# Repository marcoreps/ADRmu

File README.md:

# ADR1000 10V standard

## Scope

Low cost 10V DC reference standard in DIN 41612 modular enclosure. Based on ovenized LTZ1000 / LTZ1000A or ADR1000A zener diodes. Fits into standard 100x160mm project boxes too. The most promising strategies for configuring the zener and buffering the output are accommodated. Includes a high isolation DC-DC converter to attenuate the effects of common mode current.

## TODO

Align JP and R designators

Remove JPB and JPH enumeration

add lt5400 and other gain resistor options

discrete push-pull driver

snubber for the DC-DC converter?

## Assembly advice

Recommended 5:7 transformer (pri:sec) when using 12V input

## Spec speculations

After initial settling, tempco adjustment, continuously powered on, no ambient temperatures outside of specified range

### Output Voltage Stability (± µV/V):

24 hour: < 0.3

30 day: < 0.4

90 day: < 0.8

1 year: < 1.0

### Output Voltage Noise (0.1 - 10 Hz)(±µV/V rms)

< 0.02

### Output Voltage Tempco (±µV/V/K)

< 0.04

### Short circuit current (mA)

9-11

### Power consumption (W)

\< 2W

### Isolation (to DCin, Chassis)

\> 10 000 MΩ

< 1000 pF

### Output Protection

Output can be shorted indefinitely with battery life derating. Output protected against ESD and input up to 60V.

### Specified Temperature Range (°C)

15 - 35

### Oerational Temperature Range (°C)

-10 - 40

## Measured results
| SN    | U202  | .1-10Hz Noise   | Tempco 15-35°C    |  24h Stab  |  30d Stab  |  90d Stab  |  1yr Stab  |
| ---   | ----  | --------------  | ---------------   | ---------- | ---------- | ---------- | ---------- |
|       |       | \[µV/V rms\]    | \[µV/V/k\]        | \[µV/V\]   | \[µV/V\]   | \[µV/V\]   | \[µV/V\]   |
|   1   | ADR   | [0.0139][1]     |                   | 0.25       | 0.4        |            |            |
| ~~2~~ |~~LTZ-A~~| ~~[0.0175][2]~~|                  |            |            |            |            |
|   3   | LTZ-A | [0.0201][3]     | [-0.024][3tc]     |            |            |            |            |
|   4   |ADR1001| [0.0275][4]     | [-0.133][4tc]     |            |            |            |            |
| ~~5~~ |~~ADR~~|~~[0.0119][5]~~  |~~[+0.015][5tc]~~  |            |            |            |            |
| ~~7~~ |~~ADR~~|~~[0.0125][7]~~  |~~[+0.032][7tc]~~  |            |            |            |            |
|   9   |  ADR  |  [0.0121][9]    |  [+0.156][9tc]    |            |            |            |            |
|~~107~~|~~ADR~~|                 |~~[+0.049][107tc]~~|            |            |            |            |
|~~108~~|~~ADR~~|~~[0.0163][108]~~|~~[+0.030][108tc]~~|            |            |            |            |
|~~10~~ |~~ADR~~|~~[0.0115][10]~~ |~~[-0.028][10tc]~~ |            |            |            |            |
|  11   | ADR   | [0.0129][11]    | [+0.015][11tc]    |            |            |            |            |
|  12   | ADR   | [0.0116][12]    |                   |            |            |            |            |
|~~13~~ |~~ADR~~|~~[0.0132][13]~~ |~~[-0.024][13tc]~~ |            |            |            |            |
|~~F731B~~  |~~DH80417B~~| ~~[0.0272][731]~~  |       |            |            |            |            |
|   6   | ADR   |                 | [-0.018][6tc]     |            |            |            |            |
|~~14~~ |~~LTZ-A~~|               |~~[+0.025][14tc]~~ |            |            |            |            |
|  15   |  ADR  |   [0.0123][15]  |                   |            |            |            |            |
|  20   | LTZ-A |                 | -0.018            |            |            |            |            |
 
[1]:/results/ADRmu1_LFnoise.png
[2]:/results/ADRmu2_LFnoise.png
[3]:/results/ADRmu3_LFnoise.png
[4]:/results/ADRmu4_LFnoise_improved.png
[5]:/results/ADRmu5_LFnoise.png
[7]:/results/ADRmu7_LFnoise.png
[9]:/results/ADRmu9_LFnoise.png
[10]:/results/ADRmu10_LFnoise.png
[11]:/results/ADRmu11_LFnoise.png
[12]:/results/ADRmu12_LFnoise.png
[13]:/results/ADRmu13_LFnoise.png
[13]:/results/ADRmu15_LFnoise.png
[108]:/results/ADRmu108_LFnoise.png
[731]:/results/Fluke731B_LFnoise.png

[3tc]:/results/ADRmu3_TC.ipynb
[4tc]:/results/ADRmu4_TC.ipynb
[5tc]:/results/ADRmu5_TC.ipynb
[7tc]:/results/ADRmu7_TC.ipynb
[9tc]:/results/ADRmu9_TC.ipynb
[10tc]:/results/ADRmu10_TC.ipynb
[11tc]:/results/ADRmu11_TC.ipynb
[12tc]:/results/ADRmu12_TC.ipynb
[13tc]:/results/ADRmu13_TC.ipynb
[107tc]:/results/ADRmu107_TC.ipynb
[108tc]:/results/ADRmu108_TC.ipynb
[14tc]:/results/ADRmu14_TC.ipynb
[6tc]:/results/ADRmu6_TC.ipynb

Strikethrough: Device no longer in my possession

## Initial drift & burn-in
| SN  | PCB  |      U202      | Powered on | Preparation | Initial ΔV | Hours to plateau | .1-10Hz noise before | Special |
| --- | ---- | -------------- | ---------- | ----------- | ---------- | ---------------- | -------------------- |---------|
|   1 | 0.4  | ADR1000A 2017  | Jul 2021   |1yr dummy circuit| no data|                  |                      | VPG golden network |
|   2 | 0.4  |    LTZ1000A    | Apr 2022   | none        | no data    |                  |                      | LTZ1000A w/ VPG foil |
|   3 | 0.5  |    LTZ1000A    | Mar 2022   | none        | no data    |                  |                      | Cheapest LTZ variant |
|   4 |0.5SE |    ADR10001    | May 2022   | none        | no data    |                  |                      | ~~Popcorn noise~~ Healed? |
|   5 | 0.9  | ADR1000A 2022  | Jan 2023   | 7d 150°C b&b|            |                  |                      | Gone to new owner |
|   7 | 0.9  | ADR1000A 2022  | Jan 2023   | 7d 150°C b&b|            |                  |                      | No trim resistors |
|   9 | 0.9  | ADR1000A 2022  | Jan 2023   | none        | 1.1 µV/V   | 310              |                      | VPG golden network |
| 107 | 0.9  | ADR1000A 2018  | Dec 2022   | none        | 3.8 µV/V   | 640              |                      | Transplant to 108 |
| 108 | 0.9  | ADR1000A 2018  | Dec 2022   | none        | 3.8 µV/V   | 640              |                      | Gone to new owner |
|  10 | 0.9  | ADR1000A 2022  | Feb 2023   | none        |            |                  |                      | On/off cylcing 48h |
|  11 | 0.9  | ADR1000A 2022  | Feb 2023   |7d dummy circuit|         |                  |                      | No trim resistors |
|  12 | 0.9  | ADR1000A 2022  | Feb 2023   |7d in situ b&b|           |                  |                      | On/off cylcing 24h |
|  13 | 0.9  | ADR1000A 2022  | Feb 2023   |             |            |                  |                      | Ultrasonic cleaned |
|   6 | 1.1  | ADR1000A 2022  | Mar 2023   |30d dummy circuit|        |                  |                      | Chinese SMT assembly |
|  14 | 1.1  | LTZ1000A 2020  | Mar 2023   | none        |            |                  |                      | Chinese SMT assembly |
|  15 | 1.1  | LTZ1000A 2020  | Mar 2023   | none        |            |                  |                      | Chinese SMT assembly |
|  44 | 1.1  | LTZ1000A 2020  | Mar 2023   | none        |            |                  |                      | Chinese SMT assembly |
|  20 | 1.1  | LTZ1000A 2020  | Sep 2023   | none        |            |                  |                      | Chinese SMT assembly |

## Trim levels

The PCB is prepared for various configurations to adapt to different needs and part availabilities. Here's what I have built so far:

| SN  | U202 | R213 / Pin4 | R214 / Pin5 | R220 / Pin3 | Oven divider      | R225 / Iz Down | R223 / Iz Up | 10V gain divider |
| --- | ---- | ----------- | ----------- | ----------- | ----------------- | -------------- | ------------ | ---------------- |
|   1 | ADR  | 1445 95.3R  | 1445 61.9k  | 0R          | 1445 13 ratio     | open           | open         | 1445 2 ratio     |
|   2 |LTZ-A | Z201 100R   | 61.9k  Foil | SMD Foil    | VHD200 13 ratio   |                |              | VHD200 2.5 ratio |
|   3 |LTZ-A | 100R TOMC   | 50k S102    | 100R TOMC/5 | TDP10k 13.5 ratio | open           | 230k RN73    | TDP10k 2.5 ratio |
|   4 |ADR1k1| 100R VHP100T| integrated  | integrated  | integrated        |                |              | integrated       |
|   5 | ADR  | Alpha MCY   | Alpha MAY   | 0R          | TDP10k 11.5 ratio | open           | 470k RN73    | TDP10k 2 ratio   |
|   7 | ADR  | Z201        | Z201        | 0R          | TDP10k            | open           | open         | TDP10k 2 ratio   |
|   9 | ADR  | 1445 95.3R  | 1445 61.9k  | 0R          | 1445 13 ratio     | open           | open         | 1445 2 ratio     |
| 107 | ADR  | Z201T       | Z202T       | 0R          | TOMC10k 11.5 ratio| 200k RN73      | open         | TDP10k 2 ratio   |
| 108 | ADR  | Z201T       | Z202T       | 0R          | TOMC10k 11.5 ratio|                |              | TDP10k 2 ratio   |
|  10 | ADR  | RCK02       | RCK02       | 0R          | TDP10k 11.5 ratio | 493k RN73      | open         | TDP10k 2 ratio   |
|  11 | ADR  | Z201T       | Z201T       | 0R          | TDP10k 11.5 ratio |                |              | TDP10k 2 ratio   |
|  12 | ADR  | RCK02       | RCK02       | 0R          | TDP10k 12 ratio   | 1M             | open         | TDP10k 2 ratio   |
|  13 | ADR  | RCK02       | RCK02       | 0R          | TDP10k 11.5 ratio | open           | 1M           | TDP10k 2 ratio   |
|   6 | ADR  | PTF56       | PTF56       | 0R          | TDP10k 11.5 ratio |                |              | TDP10k 2 ratio   |
|  14 |LTZ-A | TDP         | 1% ax metal | TDP         | TDP10k 12   ratio | open           | open         | TDP10k 2.5 ratio |
|  15 |      |             |             |             |                   |                |              |                  |
|  44 | ADR  | Z201T       | Z202T       | 0R          | TDP10k 11.5 ratio | 900k           | open         | TDP10k 2 ratio   |
|  20 |LTZ-A | 100R TDP    | 40k Prec WW | 16.667R TDP | TDP10k 11.5 ratio | open           | 1M           | TDP10k 2.5 ratio |

## Raw Vz of 10 parts in datasheet default circuit, warmed up for a few minutes but not burnt in
| SN  |   Type  | Datecode |     Vz    | 
| --- | ------- | -------- | --------- |
| \#1 | ADR1000 | 2108     | 6.6556730 |
| \#8 | ADR1000 | 2108     | 6.6545676 |
| \#9 | ADR1000 | 2108     | 6.6531460 |
| \#10| ADR1000 | 2108     | 6.6609841 |
| \#11| ADR1000 | 2108     | 6.6690263 |
| \#12| ADR1000 | 2108     | 6.6534043 |
|   5 | ADR1000 | 2209     | 6.6457519 |
|   8 | ADR1000 | 2209     | 6.6509818 |
|   3 | ADR1000 | 1839     | 6.6707478 |
| \#7 | ADR1000 | 2108     | 6.6545726 |

### ADR1000 & Vishay 1445 All-in-one Resistor Network

My SN 1 is built this way. This is a no-brainer or easy mode. When I got my first glimpse at the ADR1000 datasheet I went straight to Vishay Foil Resistors and ordered an all-in-one resistor network with all the critical resistors from the datasheet plus a simple divider for buffering the 6.62V output to 10V ([Custom network specification][1445]). By specifying at least 2 ppm/°C TC tracking for the two critical dividers I am guaranteed great performance. And thanks to the hermetically sealed DIP14 package I expect little long term drift from the resistors. This solution comes at a hefty price and is not effortlessly adjustable after assembly.

[1445]:/datasheets/322146_p1-4_1445_Marco_Reps.pdf

### LTZ1000A & Discrete Vishay Foil Resistors

My SN 2 is built this way. This is probably the most popular way of building LTZ1000 voltage standards (i.e. [xDevs KX][kx]). Digikey carries quite a few hermetically sealed Vishay Bulk Metal Foil resistors ~~without MOQ these days~~ not any more LAME!, giving you all the design freedom. The two most critical parts are the LTZ-temperature-configuration divider i.e. 13k/1k and the 7.1V to 10V buffer divider i.e. 2k/5k. For these two I used hermetically sealed Vishay VHD200 dividers. These have guaranteed TC tracking and little long term drift. The remaining LTZ-configuration resistors i.e. 70k, 70k, 120R are not very critical. For best performance you can add an additional resistor to LTZ pin 3 to improve the Vrefs tempco, see "Adjusting Temperature Coefficient in Unstabilized Applications" in the LTZ1000 datasheet. 20 Ohm seems to be a reasonable approximation, suitable for most LTZs. In my case I determined 18 Ohm to be an optimal resistor with a TC peak at the oven setpoint. Careful, this additional resistor, if equipped, has a lot of influence on zener voltage and should be of high quality.

[kx]:https://xdevs.com/article/kx-ref/

### LTZ1000A & Thin film arrays

My SN 3 and 20 are built this way. This variant is inspired by Datron Wavetek 7000 DCV Standards ([EEVBlog forum thread][w7000]) and as such it has proven itself over a long time. Here the most critical voltage dividers for the LTZ1000 temperature and the 7->10V gain are implemented through an arrangement of monolithic thin film resistor arrays and their fantastic tracking temperature coefficients. Furthermore the overall output voltage tempco is fine-tuned after assembly through trim resistors R225 / R223. SN 3 is one of the cheapest ADRmus in my comparison, yet one of the most stable ones.

[w7000]:https://www.eevblog.com/forum/metrology/(3300)-wavetek-7000-the-hidden-gemstone/

### ADR1000 & Thin film arrays

Most of my ADRmus are built this way. This is the most cost-effective way to build a great performance 10V DC Standard. The same techniques that worked for LTZ in the past also apply to ADR1000, only the specific resistor values are slightly different. Based on my early ADR1000 samples I can see significantly longer initial settling times of ADR1000, which can be improved simply by power cycling a part in its default circuit (30 minutes off, 30 minutes on for a week). This new part exhibits lower low frequency noise than LTZ. A 10V buffer circuit with a low noise op amp and thin film arrays ([Excess Noise in Thin Film and Metal Foil Resistor Networks][beev]) passes this advantage right on to the output. 

[beev]:https://arxiv.org/abs/2109.02448

### ADR1001

I have been given one very early sample of this new part, so my results may not reflect the final parts performance. This new all-in-one ovenized zener reference & buffer makes it easier than ever before to deploy a high performance, environmentally tolerant voltage reference with few external parts and little research. My sample showed some popcorn noise at first ([Screenshot][popcorn]), which I seemingly improved by keeping the part powered on, externally heated to 110°C for a few weeks. This extreme measure made it impossible to judge early drift. Long-term drift and tempco now seem to fall easily within the datasheet spec. LF noise of the 10V output still appears to be slightly elevated, but the datasheet only specifies this for the 6P6 output. Overall this part is not the greatest performer in my comparison, it lacks a way of fine-tuning, but it's by far the easiest to use and its efficient overall heater makes it interesting for portable devices.

[popcorn]:/results/ADRmu4_LFnoise_popcorn.png

## Results

### Raw data

Unprocessed CSV files can be found here https://github.com/marcoreps/multiinstrumentalist/tree/master/csv These show direct readings by digital voltmeters, which are subject to temperature variations, adjustments and even modifications, resulting in large deviations of readings.

### Processed data

To attenuate voltmeter errors from the measurements, we use the mathematical difference between an ADRmu reading and the average of many ADRmu readings that were taken at the same time, with the same voltmeter. These results can be found here https://github.com/marcoreps/ADRmu/tree/main/results

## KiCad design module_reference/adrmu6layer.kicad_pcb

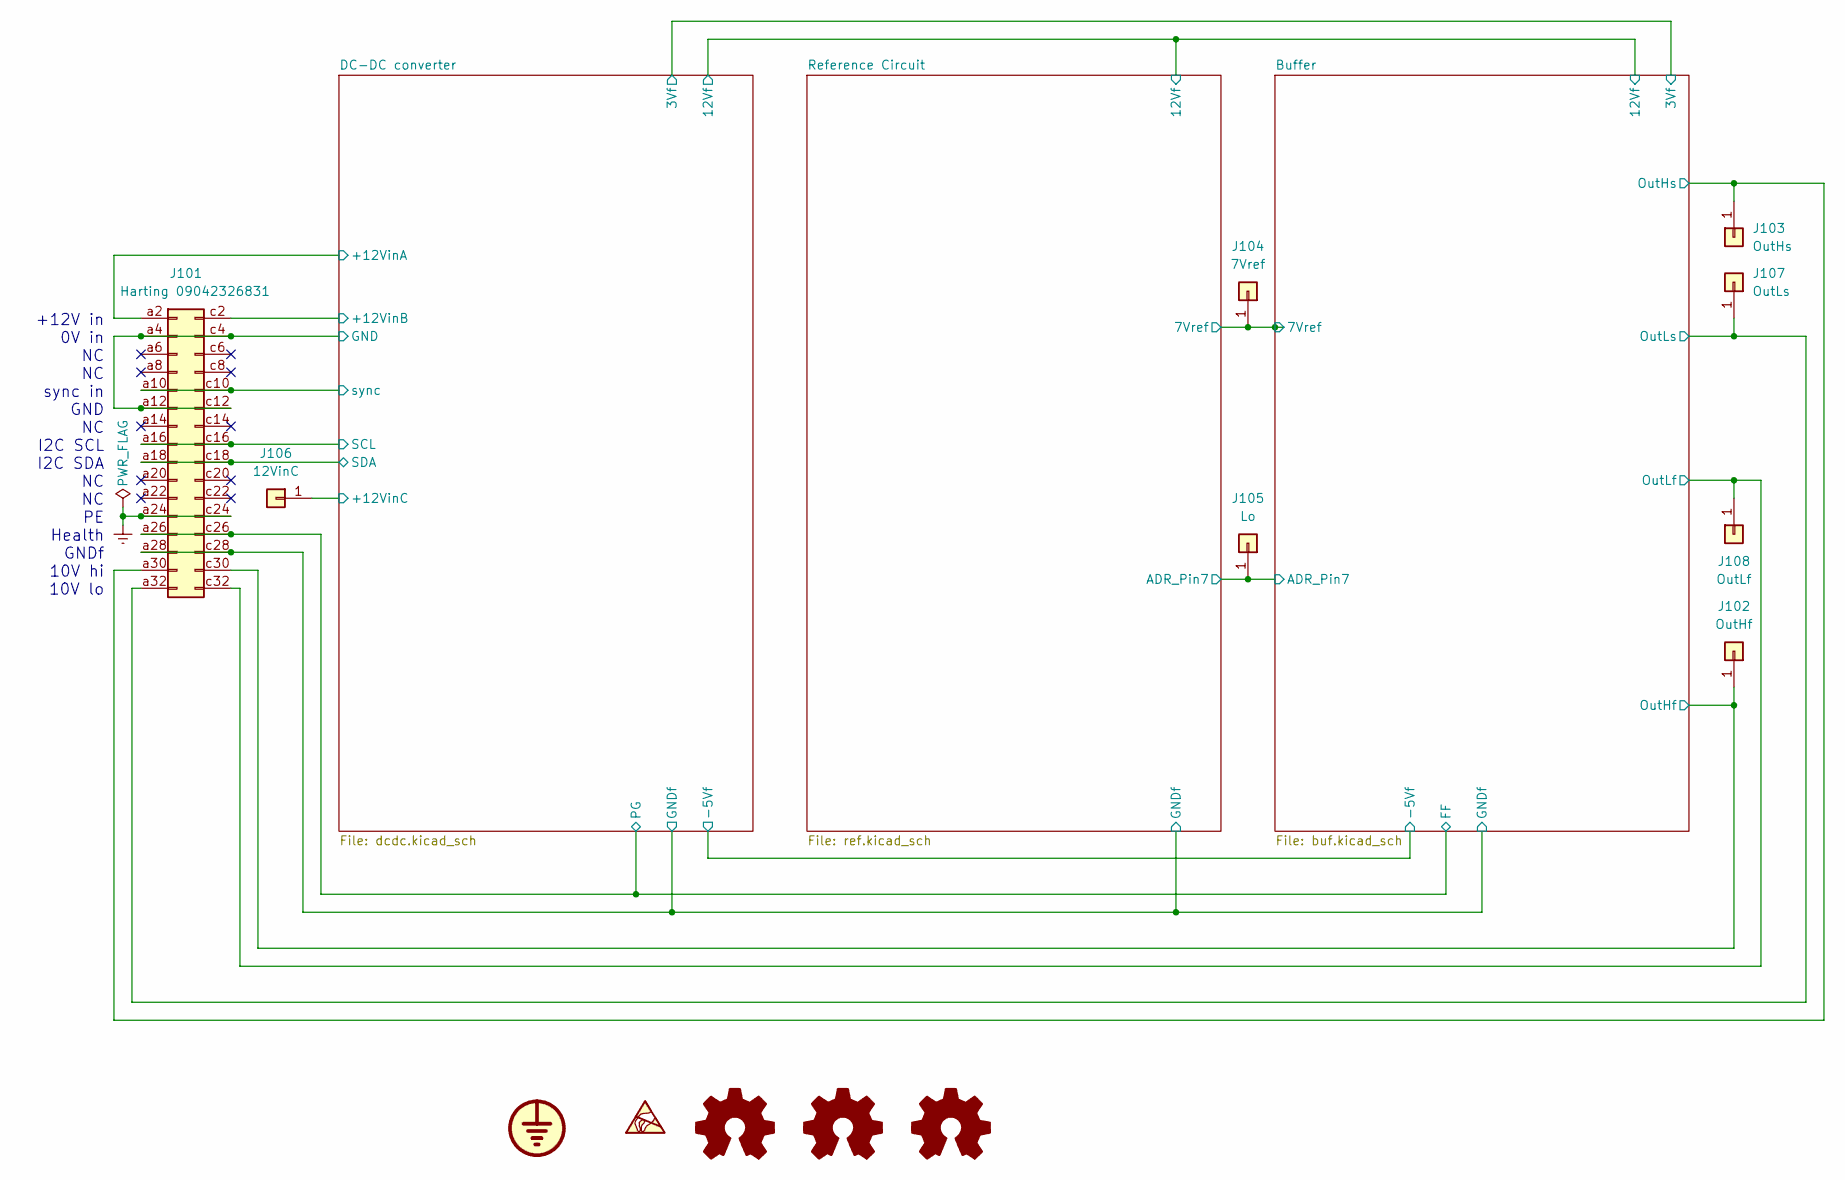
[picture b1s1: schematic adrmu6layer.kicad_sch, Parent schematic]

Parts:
J101: Harting 09042326831; DIN41612_D_2x16_Male_Horizontal_THT
J102: OutHf; SolderWire-1sqmm_1x01_D1.4mm_OD2.7mm
J103: OutHs; SolderWire-1sqmm_1x01_D1.4mm_OD2.7mm
J104: 7Vref; SolderWire-1sqmm_1x01_D1.4mm_OD3.9mm
J105: Lo; SolderWire-1sqmm_1x01_D1.4mm_OD3.9mm
J106: 12VinC; SolderWire-1sqmm_1x01_D1.4mm_OD2.7mm
J107: OutLs; SolderWire-1sqmm_1x01_D1.4mm_OD2.7mm
J108: OutLf; SolderWire-1sqmm_1x01_D1.4mm_OD2.7mm
SYM101: OSMU; osmu_logo
SYM102: SYM_ESD_Small; ESD-Logo_8.9x8mm_SilkScreen
SYM103: Logo_Open_Hardware_Small; OSHW-Logo2_9.8x8mm_SilkScreen
SYM104: Logo_Open_Hardware_Small; KiCad-Logo2_6mm_SilkScreen
SYM105: Logo_Open_Hardware_Small; moin_logo

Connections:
/Buffer/ADR_Pin7: J105.1; also elsewhere on the board
/Buffer/FF: J101.a26, J101.c26; also elsewhere on the board
/Buffer/GNDf: J101.a28, J101.c28; also elsewhere on the board
/Buffer/OutHf: J101.c30, J102.1; also elsewhere on the board
/Buffer/OutHs: J101.a30, J103.1; also elsewhere on the board
/Buffer/OutLf: J101.c32, J108.1; also elsewhere on the board
/Buffer/OutLs: J101.a32, J107.1; also elsewhere on the board
/DC-DC converter/+12VinA: J101.a2; also elsewhere on the board
/DC-DC converter/+12VinB: J101.c2; also elsewhere on the board
/DC-DC converter/+12VinC: J106.1; also elsewhere on the board
/DC-DC converter/SCL: J101.a16, J101.c16; also elsewhere on the board
/DC-DC converter/SDA: J101.a18, J101.c18; also elsewhere on the board
/DC-DC converter/sync: J101.a10, J101.c10; also elsewhere on the board
/Reference Circuit/7Vref: J104.1; also elsewhere on the board
Earth: J101.a24, J101.c24; also elsewhere on the board
GND: J101.a4, J101.a12, J101.c4, J101.c12; also elsewhere on the board

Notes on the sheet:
+12V in 0V in NC NC sync in GND NC I2C SCL I2C SDA NC NC PE Health GNDf 10V hi 10V lo

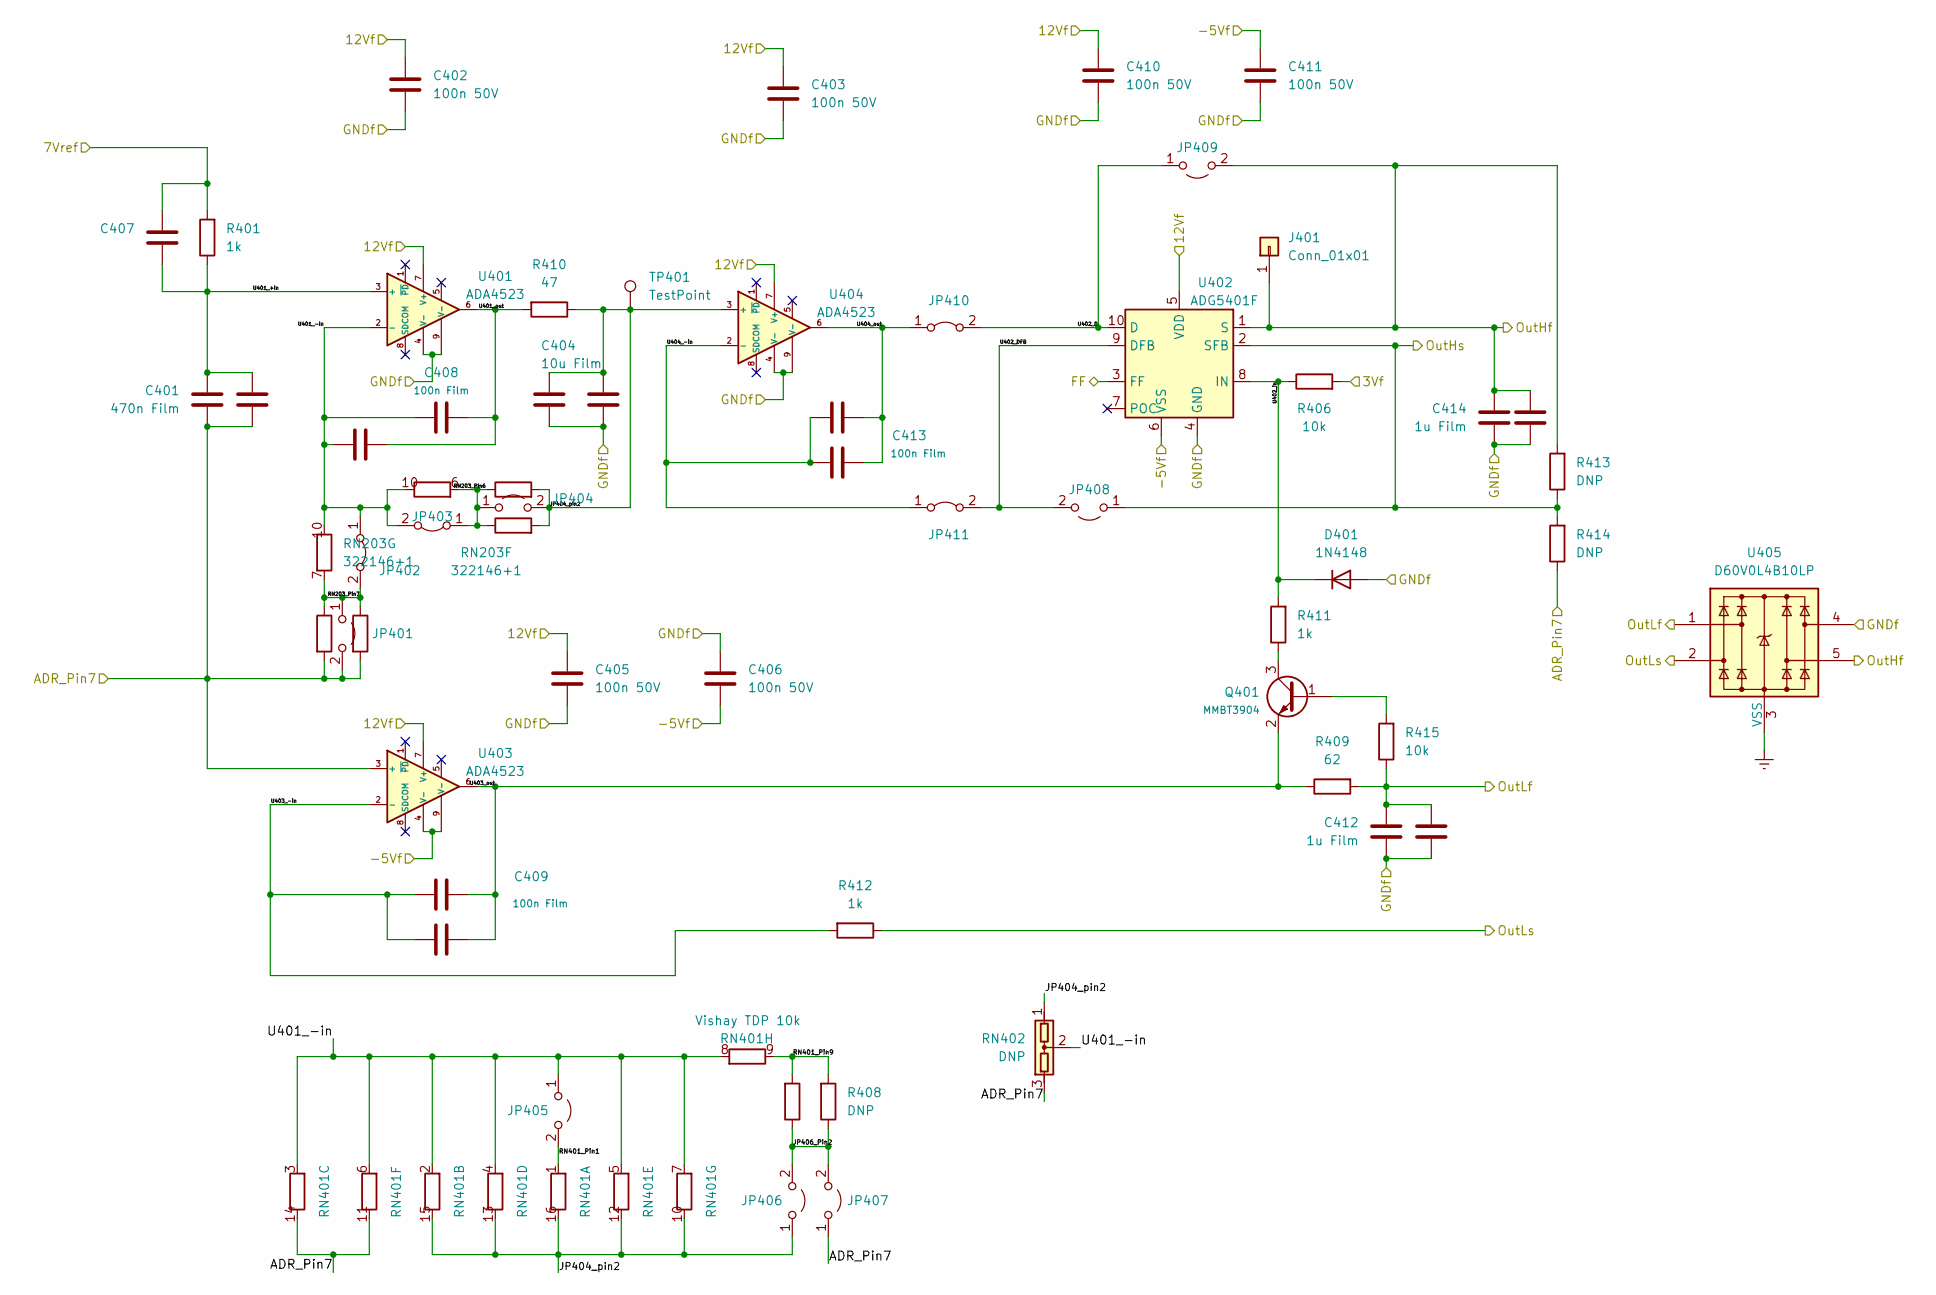
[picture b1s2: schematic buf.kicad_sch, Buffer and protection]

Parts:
C401: 470n Film; C_Rect_L7.2mm_W3.5mm_P5.00mm_FKS2_FKP2_MKS2_MKP2
C402, C403, C405, C406, C410, C411, C416, C417, C419: 100n 50V; C_0603_1608Metric
C404: 10u Film; C_Rect_L7.2mm_W11.0mm_P5.00mm_FKS2_FKP2_MKS2_MKP2
C407: DNP; C_0805_2012Metric
C408, C409, C413: 100n Film; C_Rect_L7.2mm_W2.5mm_P5.00mm_FKS2_FKP2_MKS2_MKP2
C412, C414: 1u Film; C_Rect_L4.6mm_W5.5mm_P2.50mm_MKS02_FKP02
C415: 470n; C_1206_3216Metric
C418: 22u 25V; C_1206_3216Metric
C420, C421: 1u; C_0805_2012Metric
D401: 1N4148; D_SOD-123
J401: Conn_01x01; SolderWirePad_1x01_SMD_1x2mm
JP401, JP404, JP405, JP406, JP407, JP408, JP409: Jumper_2_Open; SolderJumper-2_P1.3mm_Open_RoundedPad1.0x1.5mm
JP402, JP403, JP410, JP411: Jumper_2_Bridged; SolderJumper-2_P1.3mm_Bridged_RoundedPad1.0x1.5mm
Q401: MMBT3904; SOT-23
R401, R411, R412: 1k; R_0805_2012Metric
R402, R405: 0; Crystal_HC52-U_Vertical
R403, R404: 0; R_0805_2012Metric
R406, R415: 10k; R_0805_2012Metric
R407: DNP; Crystal_HC52-U_Vertical
R408, R413, R414: DNP; R_0805_2012Metric
R409: 62; R_0805_2012Metric
R410: 47; R_0805_2012Metric
RN203: 322146+1; VPG322146+1
RN401: Vishay TDP 10k; DIP-16_W7.62mm
RN402: DNP; Resonator-3Pin_W10.0mm_H5.0mm
TP401: TestPoint; TestPoint_THTPad_2.0x2.0mm_Drill1.0mm
U401, U403, U404: ADA4523; LFCSP-8-1EP_3x3mm_P0.5mm_EP1.6x2.34mm
U402: ADG5401F; LFCSP-10
U405: D60V0L4B10LP; Diodes_UDFN-10_1.0x2.5mm_P0.5mm

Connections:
/Buffer/3Vf: R406.2; also elsewhere on the board
/Buffer/12Vf: C402.2, C403.2, C405.2, C410.2, U401.7 (V+), U402.5 (VDD), U403.7 (V+), U404.7 (V+); also elsewhere on the board
/Buffer/-5Vf: C406.1, C411.2, U402.6 (VSS), U403.4 (V-), U403.9 (V-); also elsewhere on the board
/Buffer/ADR_Pin7: C401.1, C415.2, JP401.2 (B), JP407.1 (A), R402.2, R403.2, R414.1, RN401.11 (R6.2), RN401.14 (R3.2), RN402.3, U403.3 (+); also elsewhere on the board
/Buffer/FF: U402.3 (FF); also elsewhere on the board
/Buffer/GNDf: C402.1, C403.1, C404.2, C405.1, C406.2, C410.1, C411.1, C412.2, C414.2, C418.2, C420.2, C421.2, D401.2 (A), U401.4 (V-), U401.9 (V-), U402.4 (GND), U404.4 (V-), U404.9 (V-), U405.4; also elsewhere on the board
/Buffer/JP404_pin2: C404.1, C418.1, JP404.2 (B), JP406.1 (A), R404.2, R405.2, R410.1, RN401.10 (R7.2), RN401.12 (R5.2), RN401.13 (R4.2), RN401.15 (R2.2), RN401.16 (1.2), RN402.1, TP401.1, U404.3 (+)
/Buffer/JP406_Pin2: JP406.2 (B), JP407.2 (B), R407.1, R408.1
/Buffer/OutHf: C414.1, C421.1, J401.1, JP409.2 (B), R413.2, U402.1 (S), U405.5; also elsewhere on the board
/Buffer/OutHs: JP408.1 (A), R413.1, R414.2, U402.2 (SFB); also elsewhere on the board
/Buffer/OutLf: C412.1, C420.1, R409.2, R415.1, U405.1; also elsewhere on the board
/Buffer/OutLs: R412.1, U405.2; also elsewhere on the board
/Buffer/RN203_Pin6: JP403.1 (A), JP404.1 (A), R404.1, R405.1, RN203.6 (R6.1)
/Buffer/RN203_Pin7: JP401.1 (A), JP402.2 (B), R402.1, R403.1, RN203.7 (R7.1)
/Buffer/RN401_Pin1: JP405.2 (B), RN401.1 (1.1)
/Buffer/RN401_Pin9: R407.2, R408.2, RN401.9 (8..2)
/Buffer/U401_+in: C401.2, C407.1, C415.1, R401.1, U401.3 (+)
/Buffer/U401_-in: C408.2, C416.2, JP402.1 (A), JP403.2 (B), JP405.1 (A), RN203.10 (R7.2), RN401.2 (R2.1), RN401.3 (R3.1), RN401.4 (R4.1), RN401.5 (R5.1), RN401.6 (R6.1), RN401.7 (R7.1), RN401.8 (1.1), RN402.2, U401.2 (-)
/Buffer/U401_out: C408.1, C416.1, R410.2, U401.6
/Buffer/U402_D: JP409.1 (A), JP410.2 (B), U402.10 (D)
/Buffer/U402_DFB: JP408.2 (B), JP411.2 (B), U402.9 (DFB)
/Buffer/U402_in: D401.1 (K), R406.1, R411.2, U402.8 (IN)
/Buffer/U403_-in: C409.2, C417.2, R412.2, U403.2 (-)
/Buffer/U403_out: C409.1, C417.1, Q401.2 (E), R409.1, U403.6
/Buffer/U404_-in: C413.2, C419.2, JP411.1 (A), U404.2 (-)
/Buffer/U404_out: C413.1, C419.1, JP410.1 (A), U404.6
/Reference Circuit/7Vref: C407.2, R401.2; also elsewhere on the board
Earth: U405.3 (VSS), U405.8 (VSS); also elsewhere on the board
unnamed: Q401.1 (B), R415.2
unnamed: Q401.3 (C), R411.1

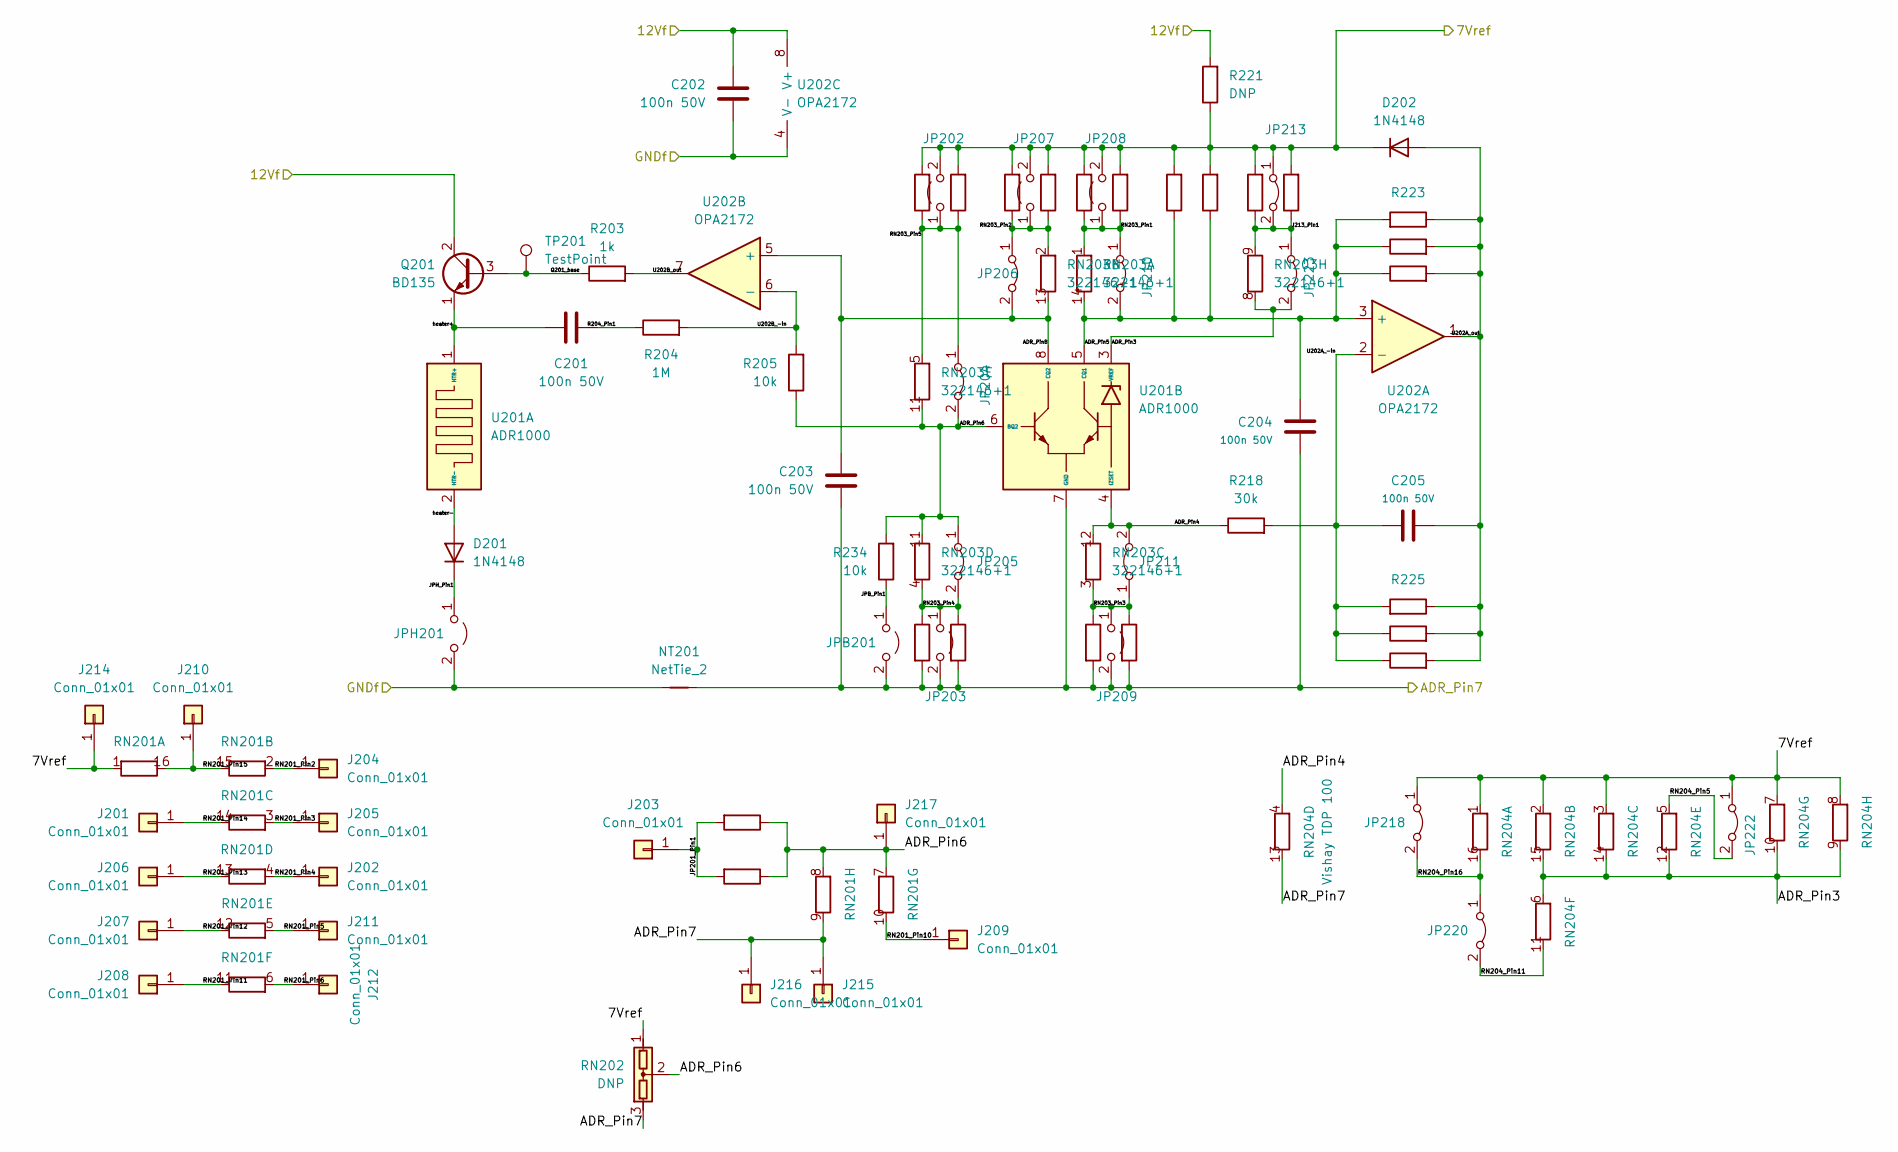
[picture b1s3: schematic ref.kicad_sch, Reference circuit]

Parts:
C201, C202, C203, C204, C205: 100n 50V; C_0603_1608Metric
D201, D202: 1N4148; D_SOD-123
J201, J202, J203, J204, J205, J206, J207, J208, J209, J210, J211, J212, J214, J215, J216, J217: Conn_01x01; SolderWire-0.1sqmm_1x01_D0.4mm_OD1mm
JP202, JP203, JP207, JP208, JP209: Jumper_2_Open; SolderJumper-2_P1.3mm_Open_RoundedPad1.0x1.5mm
JP204, JP205, JP206, JP210, JP211, JP213, JP218, JP220, JP222, JP223: Jumper_2_Bridged; SolderJumper-2_P1.3mm_Bridged_RoundedPad1.0x1.5mm
JPB201: Jumper_2_Open; SolderJumper-2_P1.3mm_Open_RoundedPad1.0x1.5mm
JPH201: Jumper_2_Open; SolderJumper-2_P1.3mm_Open_RoundedPad1.0x1.5mm
NT201: NetTie_2; NetTie-2_SMD_Pad2.0mm
Q201: BD135; TO-126-3_Vertical
R201, R206, R209, R212, R215, R219: 0; R_0805_2012Metric
R202, R207, R208, R211, R213, R214, R220: 0; Crystal_HC52-U_Vertical
R203: 1k; R_0805_2012Metric
R204: 1M; R_0805_2012Metric
R205, R234: 10k; R_0805_2012Metric
R210: 62k; R_0805_2012Metric
R216, R221: DNP; R_0805_2012Metric
R217: DNP; Crystal_HC52-U_Vertical
R218: 30k; R_0805_2012Metric
R222, R224, R226, R227: TBD; R_0805_2012Metric
R223, R225: TBD; Crystal_HC52-U_Vertical
RN201: Vishay TDP 10k; DIP-16_W7.62mm
RN202: DNP; Resonator-3Pin_W10.0mm_H5.0mm
RN203: 322146+1; VPG322146+1
RN204: Vishay TDP 100; DIP-16_W7.62mm
TP201: TestPoint; TestPoint_THTPad_2.0x2.0mm_Drill1.0mm
U201: ADR1000; TO-5-8
U202: OPA2172; SOIC-8_3.9x4.9mm_P1.27mm

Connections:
/Buffer/12Vf: C202.2, Q201.2 (C), R221.2, U202.8 (V+); also elsewhere on the board
/Buffer/ADR_Pin7: C203.1, C204.1, J215.1, J216.1, JP203.2 (B), JP209.2 (B), JPB201.2 (B), NT201.2, R207.2, R209.2, R213.2, R215.2, RN201.9 (8..2), RN202.3, RN204.13 (R4.2), U201.7 (GND); also elsewhere on the board
/Buffer/GNDf: C202.1, JPH201.2 (B), NT201.1, U202.4 (V-); also elsewhere on the board
/Reference Circuit/7Vref: D202.1 (K), J214.1, JP202.2 (B), JP207.2 (B), JP208.2 (B), JP213.1 (A), JP218.1 (A), JP222.1 (A), R206.2, R208.2, R210.2, R211.2, R212.2, R214.2, R216.2, R217.2, R219.2, R220.2, R221.1, RN201.1 (1.1), RN202.1, RN204.1 (1.1), RN204.2 (R2.1), RN204.3 (R3.1), RN204.7 (R7.1), RN204.8 (1.1); also elsewhere on the board
/Reference Circuit/ADR_Pin3: JP223.2 (B), RN203.8 (1.1), RN204.6 (R6.1), RN204.9 (8..2), RN204.10 (R7.2), RN204.12 (R5.2), RN204.14 (R3.2), RN204.15 (R2.2), U201.3 (VREF)
/Reference Circuit/ADR_Pin4: JP211.2 (B), R218.1, RN203.12 (R3.2), RN204.4 (R4.1), U201.4 (IZSET)
/Reference Circuit/ADR_Pin5: C204.2, JP210.2 (B), R216.1, R217.1, R222.1, R223.2, R226.1, RN203.14 (1.2), U201.5 (CQ1), U202.3 (+)
/Reference Circuit/ADR_Pin6: J217.1, JP204.2 (B), JP205.1 (A), R201.1, R202.1, R205.1, R234.2, RN201.7 (R7.1), RN201.8 (1.1), RN202.2, RN203.11 (R5.2), U201.6 (BQ2)
/Reference Circuit/ADR_Pin8: C203.2, JP206.2 (B), RN203.13 (R2.2), U201.8 (CQ2), U202.5 (+)
/Reference Circuit/J213_Pin1: JP213.2 (B), JP223.1 (A), R219.1, R220.1, RN203.9 (8..2)
/Reference Circuit/JP201_Pin1: J203.1, R201.2, R202.2
/Reference Circuit/JPB_Pin1: JPB201.1 (A), R234.1
/Reference Circuit/JPH_Pin1: D201.1 (K), JPH201.1 (A)
/Reference Circuit/Q201_base: Q201.3 (B), R203.1, TP201.1
/Reference Circuit/R204_Pin1: C201.2, R204.1
/Reference Circuit/RN201_Pin2: J204.1, RN201.2 (R2.1)
/Reference Circuit/RN201_Pin3: J205.1, RN201.3 (R3.1)
/Reference Circuit/RN201_Pin4: J202.1, RN201.4 (R4.1)
/Reference Circuit/RN201_Pin5: J211.1, RN201.5 (R5.1)
/Reference Circuit/RN201_Pin6: J212.1, RN201.6 (R6.1)
/Reference Circuit/RN201_Pin10: J209.1, RN201.10 (R7.2)
/Reference Circuit/RN201_Pin11: J208.1, RN201.11 (R6.2)
/Reference Circuit/RN201_Pin12: J207.1, RN201.12 (R5.2)
/Reference Circuit/RN201_Pin13: J206.1, RN201.13 (R4.2)
/Reference Circuit/RN201_Pin14: J201.1, RN201.14 (R3.2)
/Reference Circuit/RN201_Pin15: J210.1, RN201.15 (R2.2), RN201.16 (1.2)
/Reference Circuit/RN203_Pin1: JP208.1 (A), JP210.1 (A), R212.1, R214.1, RN203.1 (1.1)
/Reference Circuit/RN203_Pin2: JP206.1 (A), JP207.1 (A), R210.1, R211.1, RN203.2 (R2.1)
/Reference Circuit/RN203_Pin3: JP209.1 (A), JP211.1 (A), R213.1, R215.1, RN203.3 (R3.1)
/Reference Circuit/RN203_Pin4: JP203.1 (A), JP205.2 (B), R207.1, R209.1, RN203.4 (R4.1)
/Reference Circuit/RN203_Pin5: JP202.1 (A), JP204.1 (A), R206.1, R208.1, RN203.5 (R5.1)
/Reference Circuit/RN204_Pin5: JP222.2 (B), RN204.5 (R5.1)
/Reference Circuit/RN204_Pin11: JP220.2 (B), RN204.11 (R6.2)
/Reference Circuit/RN204_Pin16: JP218.2 (B), JP220.1 (A), RN204.16 (1.2)
/Reference Circuit/U202A_-in: C205.2, R218.2, R224.1, R225.2, R227.1, U202.2 (-)
/Reference Circuit/U202A_out: C205.1, D202.2 (A), R222.2, R223.1, R224.2, R225.1, R226.2, R227.2, U202.1
/Reference Circuit/U202B_-in: R204.2, R205.2, U202.6 (-)
/Reference Circuit/U202B_out: R203.2, U202.7
/Reference Circuit/heater+: C201.1, Q201.1 (E), U201.1 (HTR+)
/Reference Circuit/heater-: D201.2 (A), U201.2 (HTR-)
